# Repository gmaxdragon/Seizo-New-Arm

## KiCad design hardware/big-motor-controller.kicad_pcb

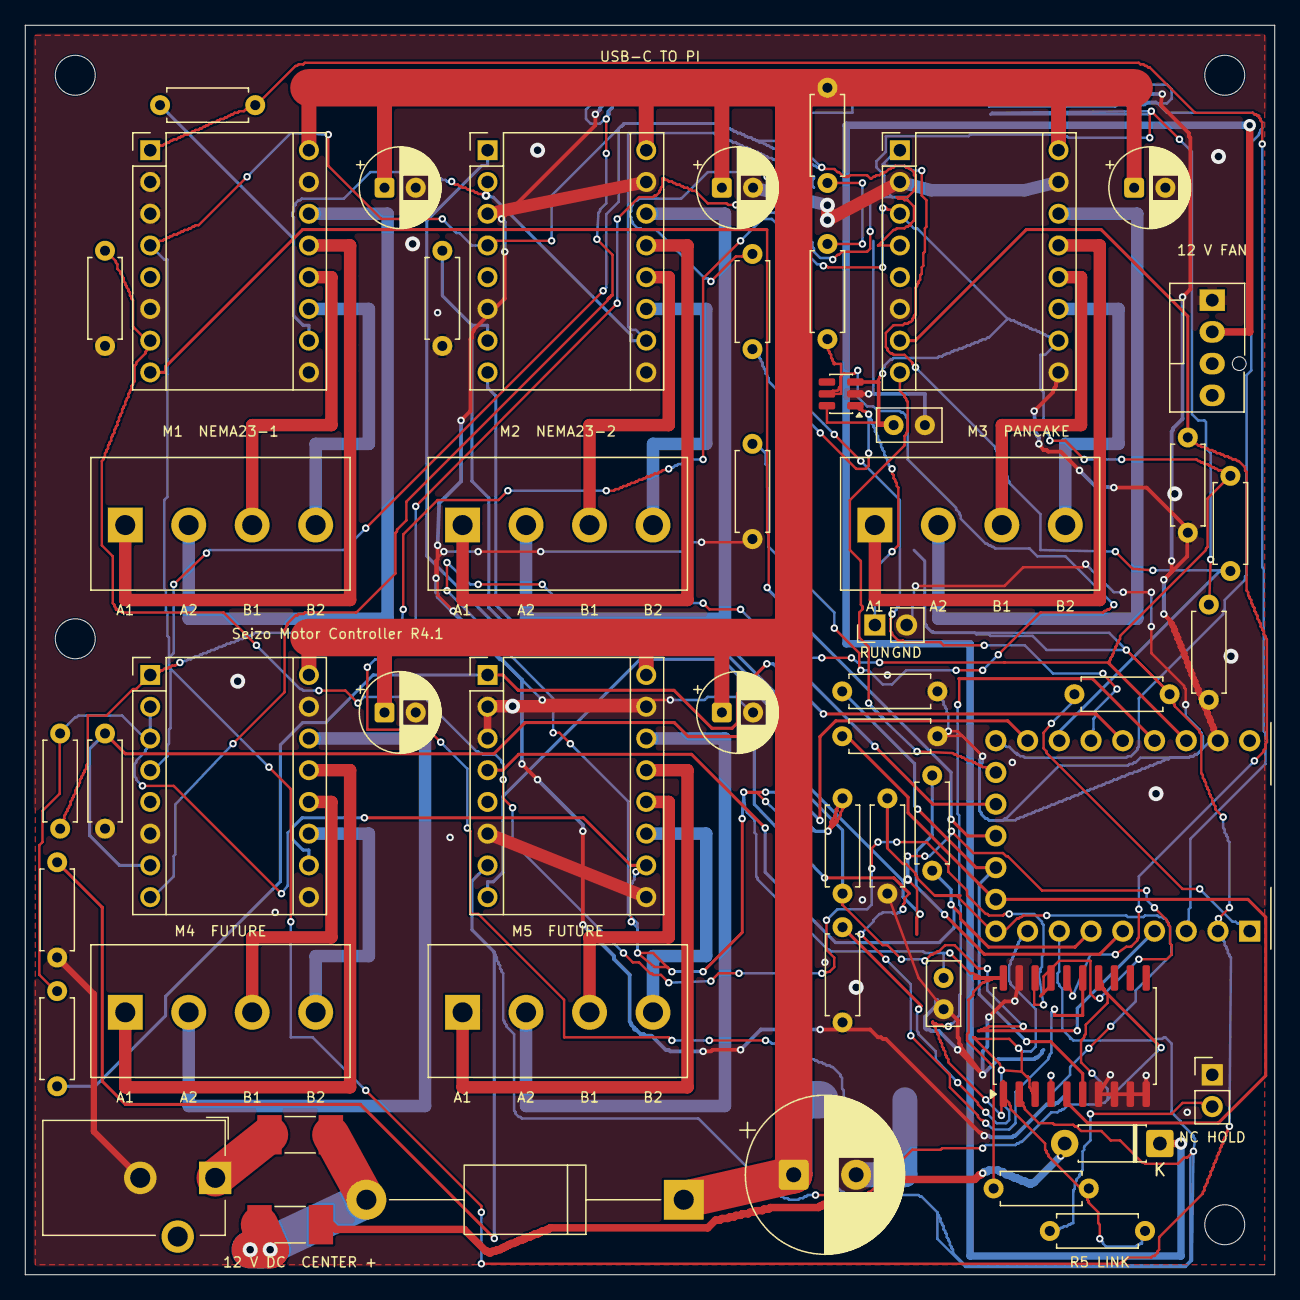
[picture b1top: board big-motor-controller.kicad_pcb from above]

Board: 2 copper layers, 100.0 x 100.0 mm, 57 parts (1 on the bottom side), 56 nets.

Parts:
C1: 470u /50V; CP_Radial_D12.5mm_P5.00mm
C2, C3: 100n /50V; C_Disc_D5.0mm_W2.5mm_P2.50mm
C11, C12, C13, C14, C15: 100u /35V; CP_Radial_D6.3mm_P2.50mm
D1: SB560-E3/54 / input isolation; D_DO-201AD_P25.40mm_Horizontal_D1.60
D2: SMCJ15A / transient clamp; D_SMC
D3: 1N5819-E3/54 / fan isolation; D_DO-41_SOD81_P7.62mm_Horizontal
F1: 4A 125VDC SLO-BLO; Fuse_Littelfuse-NANO2-451_453
F2: 0.5A 125VDC FAN; Fuse_Littelfuse-NANO2-451_453
H1, H2, H3, H4: M3 mounting; MountingHole_3.2mm_M3
J1: MOTOR1 / A1 A2 B1 B2; TerminalBlock_DORABO_DB128V_1x04_P5.08mm_D1.60
J2: MOTOR2 / A1 A2 B1 B2; TerminalBlock_DORABO_DB128V_1x04_P5.08mm_D1.60
J3: MOTOR3 / A1 A2 B1 B2; TerminalBlock_DORABO_DB128V_1x04_P5.08mm_D1.60
J4: MOTOR4 / A1 A2 B1 B2; TerminalBlock_DORABO_DB128V_1x04_P5.08mm_D1.60
J5: MOTOR5 / A1 A2 B1 B2; TerminalBlock_DORABO_DB128V_1x04_P5.08mm_D1.60
J6: PJ-102AH / 5.5mm plug,2.0mm centerpin; BarrelJack_CUI_PJ-102AH_Horizontal
J7: HOLD NC / dry contact only; PinHeader_1x02_P2.54mm_Vertical
J8: 12 V PC FAN / 1 GND, 2 +12 V, 3 TACH NC, 4 PWM NC; FanPinHeader_1x04_P2.54mm_Vertical
J9: RUN HARNESS / 1 RESET_N, 2 GND; PinHeader_1x02_P2.54mm_Vertical
R2, R3, R4, R8: 1k; R_Axial_DIN0207_L6.3mm_D2.5mm_P7.62mm_Horizontal
R5: 0R / FITTED WIRE LINK; R_Axial_DIN0207_L6.3mm_D2.5mm_P7.62mm_Horizontal
R6, R7, R9, R11, R12, R13, R14, R15, R21, R22, R23, R24, R25, R31, R32, R33, R34, R35: 10k; R_Axial_DIN0207_L6.3mm_D2.5mm_P7.62mm_Horizontal
U1, U5: BTT TMC2209 V1.3 / address 0; StepStick_Socket16_P12.70_D1.00
U2: BTT TMC2209 V1.3 / address 1; StepStick_Socket16_P12.70_D1.00
U3: BTT TMC2209 V1.3 / address 2; StepStick_Socket16_P12.70_D1.00
U4: BTT TMC2209 V1.3 / address 3; StepStick_Socket16_P12.70_D1.00
U6: Waveshare RP2040-Zero-M / native USB-C; Waveshare_RP2040_Zero_Headers_9_9_5_P2.54
U7: SN74HC541DWR; SOIC-20W_7.5x12.8mm_P1.27mm
U8: TPS3808G01DBVR; SOT-23-6

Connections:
/+3V3_USB: C2.1, C3.1, R4.1, R9.1, R31.1, R32.1, R33.1, R34.1, R35.1, U1.10, U2.2, U2.10, U3.3, U3.10, U4.2, U4.3, U4.10, U5.10, U6.21, U7.20, U8.3, U8.6
/A1_1: J1.1, U1.13
/A1_2: J2.1, U2.13
/A1_3: J3.1, U3.13
/A1_4: J4.1, U4.13
/A1_5: J5.1, U5.13
/A2_1: J1.2, U1.14
/A2_2: J2.2, U2.14
/A2_3: J3.2, U3.14
/A2_4: J4.2, U4.14
/A2_5: J5.2, U5.14
/B1_1: J1.3, U1.12
/B1_2: J2.3, U2.12
/B1_3: J3.3, U3.12
/B1_4: J4.3, U4.12
/B1_5: J5.3, U5.12
/B2_1: J1.4, U1.11
/B2_2: J2.4, U2.11
/B2_3: J3.4, U3.11
/B2_4: J4.4, U4.11
/B2_5: J5.4, U5.11
/DIR1: U1.8, U6.12
/DIR2: U2.8, U6.13
/DIR3: U3.8, U6.14
/DIR4: U4.8, U6.15
/DIR5: U5.8, U6.16
/EN1_N: R31.2, U1.1, U6.3
/EN2_N: R32.2, U2.1, U6.4
/EN3_N: R33.2, U3.1, U6.17
/EN4_N: R34.2, U4.1, U6.18
/EN5_N: R35.2, U5.1, U6.19
/FAN_FUSED: D3.2, F2.2
/FAN_VMOT: D3.1, J8.2
/GND: C1.2, C2.2, C3.2, C11.2, C12.2, C13.2, C14.2, C15.2, D2.2, J6.2, J7.1, J8.1, J9.2, R8.2, R11.2, R12.2, R13.2, R14.2, R15.2, R21.2, R22.2, R23.2, R24.2, R25.2, U1.2, U1.3, U1.6, U1.9, U1.15, U2.3, U2.6, U2.9, U2.15, U3.2, U3.6, U3.9, U3.15, U4.6, U4.9, U4.15, U5.2, U5.3, U5.6, U5.9, U5.15, U6.22, U7.7, U7.8, U7.9, U7.10, U7.19, U8.2
/HOLD_CONTACT: J7.2, R5.1
/HOLD_OPEN: R4.2, R5.2, U6.20, U7.1
/STEP1: R21.1, U1.7, U7.18
/STEP2: R22.1, U2.7, U7.17
/STEP3: R23.1, U3.7, U7.16
/STEP4: R24.1, U4.7, U7.15
/STEP5: R25.1, U5.7, U7.14
/STEP_RAW1: R11.1, U6.7, U7.2
/STEP_RAW2: R12.1, U6.8, U7.3
/STEP_RAW3: R13.1, U6.9, U7.4
/STEP_RAW4: R14.1, U6.10, U7.5
/STEP_RAW5: R15.1, U6.11, U7.6
/UART_A: R2.2, U1.4, U2.4, U3.4, U4.4, U6.2
/UART_A_TX: R2.1, U6.1
/UART_B: R3.2, U5.4, U6.6
/UART_B_TX: R3.1, U6.5
/VIN_FUSED: D1.2, F1.2, F2.1
/VIN_RAW: F1.1, J6.1
/VMOT: C1.1, C11.1, C12.1, C13.1, C14.1, C15.1, D1.1, D2.1, R6.1, U1.16, U2.16, U3.16, U4.16, U5.16
/VMOT_DIV_MID: R6.2, R7.1
/VMOT_RESET_N: J9.1, R9.2, U8.1
/VMOT_SENSE: R7.2, R8.1, U8.5
